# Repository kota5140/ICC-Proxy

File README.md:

# ICC-Proxy

A pass-through board that sits between an ISO/IEC 7816 contact smart card (ID-1 size) and a card reader, so the signals can be probed with a logic analyzer.
The card connector is an Amphenol FCI **7434L0825S01LF**.

> **Status**: Use at your own risk.

## Overview

| Item | Details |
|---|---|
| Outline | 168.0 × 53.98 mm (card width over the whole length) |
| Layers / thickness | 2 layers, FR-4, **0.8 mm** |
| Surface finish | **ENIG** (gold) |
| Card section | The first 85.6 mm is an ISO/IEC 7810 ID-1 outline with ISO/IEC 7816-2 contacts C1–C8 on the top side |
| Card connector (J2) | Amphenol FCI 7434L0825S01LF (through-hole) |
| Probe header (J3) | 2×5 pins, 2.54 mm pitch (optional) |
| Circuit | C1–C8 wired 1:1. No active parts |

- Nothing protrudes on either side within the first 93 mm, so the card section can be inserted fully into a reader.
- The connector is rotated 90°. Insert the card from the long edge marked `CARD IN HERE`, **chip side down, chip end first**. The card sticks out sideways by about 43 mm.
- Both layers have a GND (C5) copper pour. On the top side the pour starts behind the contact area.

## J3 pinout

| Pin | Signal | Pin | Signal |
|---|---|---|---|
| 1 | C1 VCC | 2 | C5 GND |
| 3 | C2 RST | 4 | C6 VPP |
| 5 | C3 CLK | 6 | C7 I/O |
| 7 | C4 | 8 | C8 |
| 9 | GND | 10 | GND |

S1 and S2 on J2 are the terminals of the connector's built-in card-detect switch. They are not connected to anything (solder them anyway for mechanical strength).

## Files

| Path | Contents |
|---|---|
| `gerber/ICC-Proxy_revB2_gerber_JLCPCB.zip` | Gerber and drill files for ordering (upload as is) |
| `gerber/` | The contents of the ZIP above |
| `kicad/` | Board file created with KiCad 7 (there is no schematic; newer KiCad versions will report that the file was created by an older version) |
| `docs/print_1to1_A4.pdf` | 1:1 check print (A4 landscape, with a 100 mm reference line) |

## Ordering settings (JLCPCB example)

| Option | Setting |
|---|---|
| Layers | 2 |
| PCB thickness | **0.8 mm** |
| Surface finish | **ENIG** |
| Via covering | Tented |
| Board outline tolerance | ±0.1 mm (Precision) recommended |
| Mark on PCB | Remove mark |
| Gold fingers | No |
| PCB assembly | Not used (edge rails would be added and change the board width) |

## Parts

- Amphenol FCI 7434L0825S01LF × 1
- Pin header 2×5, 2.54 mm pitch × 1 (optional)
- M2 self-tapping screws × 2 (optional, to fix the connector)

## References

- [id-1_proxy](https://git.cuvoodoo.info/kingkevin/id-1_proxy) by kingkevin (a board for the same purpose; this board is a new design made to fit a connector that is currently available)
- [ISO 7816 smartcard interface monitor](https://www.cl.cam.ac.uk/~mgk25/cardmonitor) by Markus Kuhn

## License

This project is licensed under the [CERN Open Hardware Licence Version 2 - Permissive](LICENSE) (CERN-OHL-P-2.0).

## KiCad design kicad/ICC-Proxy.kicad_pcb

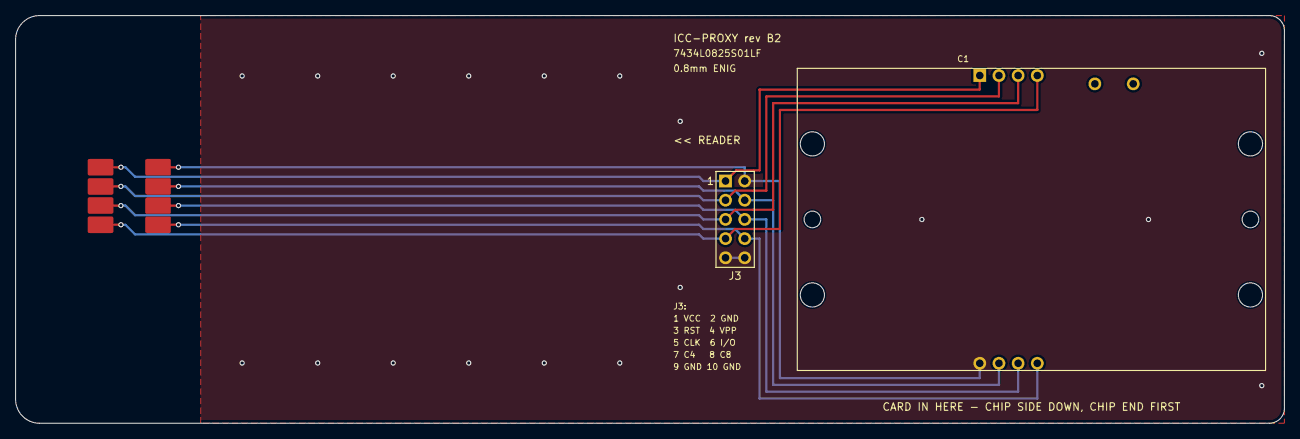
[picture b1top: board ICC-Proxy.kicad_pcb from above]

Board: 2 copper layers, 168.0 x 54.0 mm, 3 parts (0 on the bottom side), 8 nets.

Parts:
J1: ISO7816-2 contacts
J2: 7434L0825S01LF
J3: Header 2x5 2.54mm

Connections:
C4: J1.4, J2.4, J3.7
C8: J1.8, J2.8, J3.8
CLK_C3: J1.3, J2.3, J3.5
GND_C5: J1.5, J2.5, J3.2, J3.9, J3.10
IO_C7: J1.7, J2.7, J3.6
RST_C2: J1.2, J2.2, J3.3
VCC_C1: J1.1, J2.1, J3.1
VPP_C6: J1.6, J2.6, J3.4
